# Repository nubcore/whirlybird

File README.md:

# whirlybird
Direction Finder, Compass, IMU and Telemetry Transmitter

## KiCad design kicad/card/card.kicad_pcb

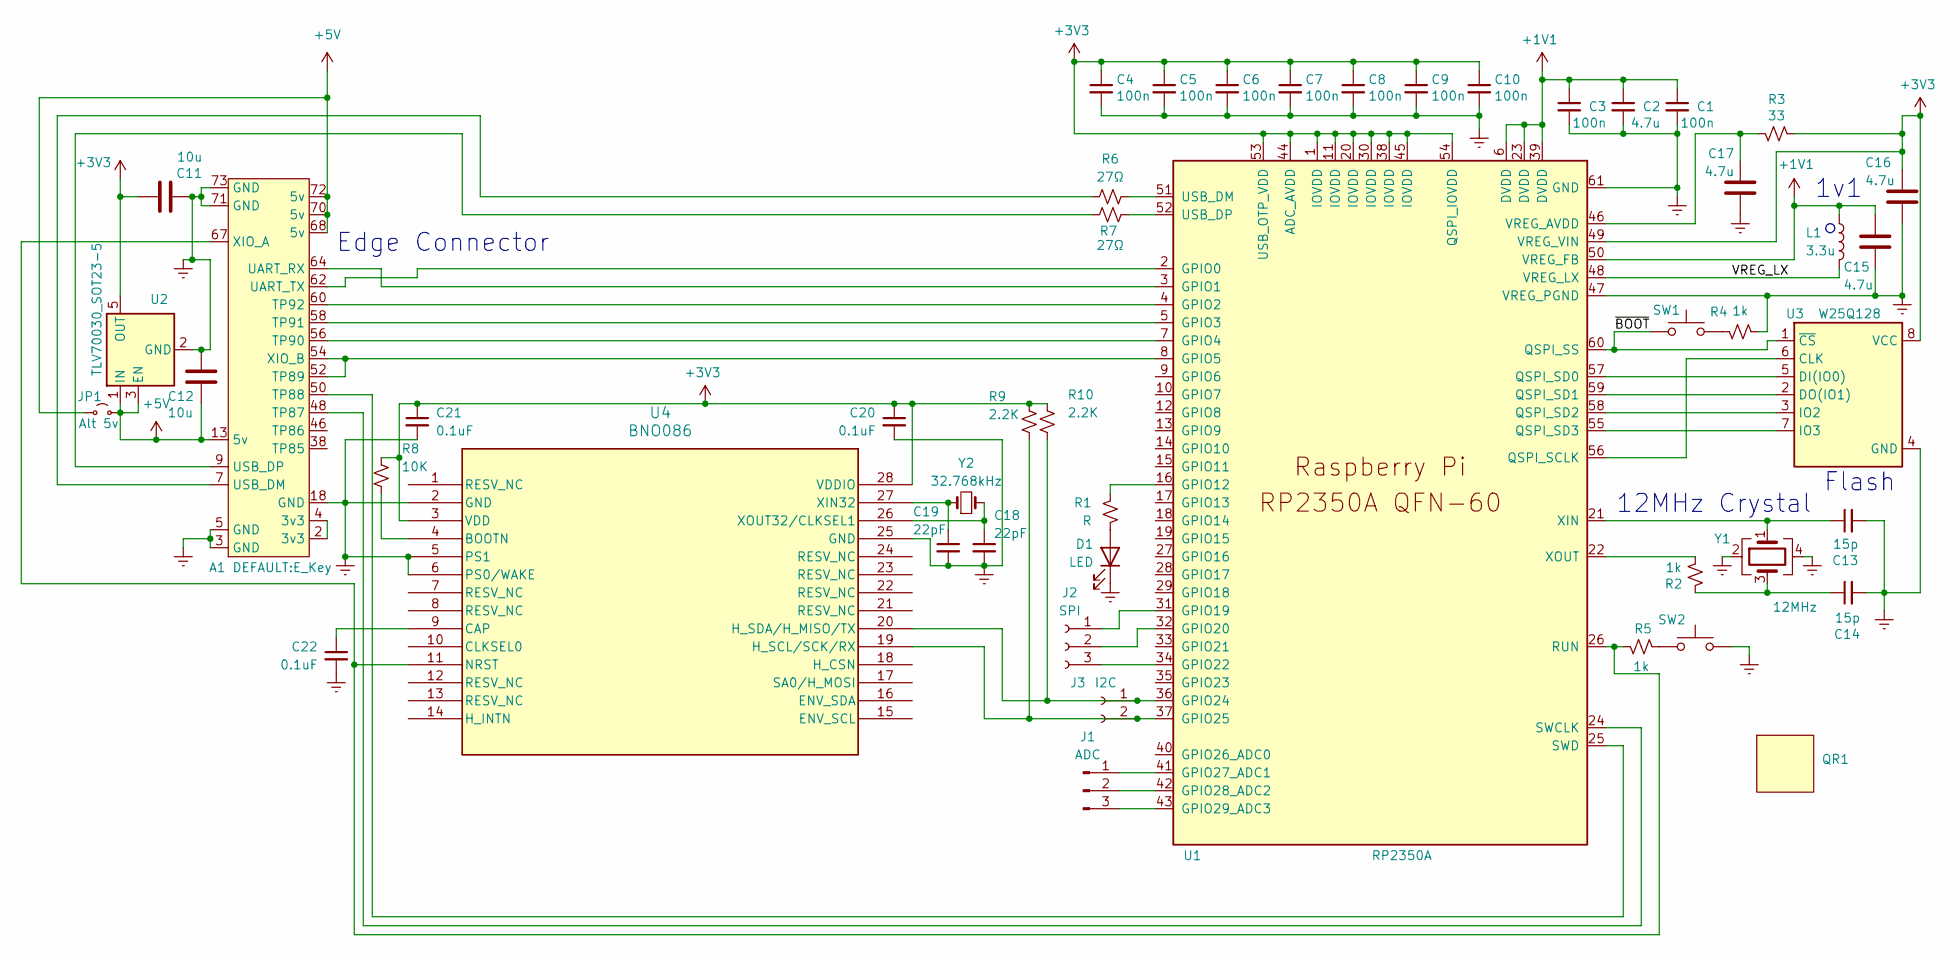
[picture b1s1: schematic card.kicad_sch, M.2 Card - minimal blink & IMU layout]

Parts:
A1: E_Key
C1, C3, C4, C5, C6, C7, C8, C9, C10: 100n; C_0402_1005Metric
C2, C17: 4.7u; C_0402_1005Metric
C11, C12: 10u; C_0805_2012Metric
C13, C14: 15p; C_0402_1005Metric
C15, C16: 4.7u; C_0402_1005Metric_small_pads
C18, C19: 22pF; C_0402_1005Metric
C20, C21, C22: 0.1uF; C_0402_1005Metric
D1: LED; LED_0603_1608Metric_Pad1.05x0.95mm_HandSolder
J1: ADC; PinHeader_1x03_P2.00mm_Vertical
J2: SPI; PinHeader_1x03_P2.00mm_Vertical
J3: I2C; PinHeader_1x02_P2.00mm_Vertical
JP1: Alt 5v; SolderJumper-2_P1.3mm_Open_TrianglePad1.0x1.5mm
L1: 3.3u; L_pol_2016
QR1: QR_8x8
R1: R; R_0603_1608Metric_Pad0.98x0.95mm_HandSolder
R2, R4, R5: 1k; R_0402_1005Metric
R3: 33; R_0402_1005Metric
R6, R7: 27Ω; R_0402_1005Metric
R8: 10K; R_0402_1005Metric
R9, R10: 2.2K; R_0402_1005Metric
SW1: USB_BOOT; SW_Push_1P1T_NO_Vertical_Wuerth_434133025816
SW2: RESET; SW_Push_1P1T_NO_Vertical_Wuerth_434133025816
U1: RP2350A; RP2350-QFN-60-1EP_7x7_P0.4mm_EP3.4x3.4mm_ThermalVias
U2: TLV70030_SOT23-5; SOT-23-5
U3: W25Q128; SOIC-8_5.23x5.23mm_P1.27mm
U4: BNO086; QFN28_BNO086_CEV
Y1: 12MHz; Crystal_SMD_3225-4Pin_3.2x2.5mm
Y2: 32.768kHz; Crystal_SMD_2012-2Pin_2.0x1.2mm

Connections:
+1V1: C1.1, C2.1, C3.1, C15.1, L1.1, U1.6 (DVDD), U1.23 (DVDD), U1.39 (DVDD), U1.50 (VREG_FB)
+3V3: C4.1, C5.1, C6.1, C7.1, C8.1, C9.1, C10.1, C11.1, C16.1, C20.1, C21.1, R3.1, R8.1, R9.1, R10.1, U1.1 (IOVDD), U1.11 (IOVDD), U1.20 (IOVDD), U1.30 (IOVDD), U1.38 (IOVDD), U1.44 (ADC_AVDD), U1.45 (IOVDD), U1.49 (VREG_VIN), U1.53 (USB_OTP_VDD), U1.54 (QSPI_IOVDD), U2.5 (OUT), U3.8 (VCC), U4.3 (VDD), U4.28 (VDDIO); also elsewhere on the board
+5V: A1.13 (5v), A1.68 (5v), A1.70 (5v), A1.72 (5v), C12.2, JP1.1 (A), JP1.2 (B), U2.1 (IN), U2.3 (EN); also elsewhere on the board
/VREG_LX: L1.2, U1.48 (VREG_LX)
/~BOOT: SW1.2, U1.60 (QSPI_SS), U3.1 (~CS)
GND: A1.3 (GND), A1.5 (GND), A1.18 (GND), A1.71 (GND), A1.73 (GND), C1.2, C2.2, C3.2, C4.2, C5.2, C6.2, C7.2, C8.2, C9.2, C10.2, C11.2, C12.1, C13.2, C14.2, C15.2, C16.2, C17.2, C18.2, C19.2, C20.2, C21.2, C22.2, D1.1 (K), R4.2, SW2.1, U1.47 (VREG_PGND), U1.61 (GND), U2.2 (GND), U3.4 (GND), U4.2 (GND), U4.5 (PS1), U4.6 (PS0/WAKE), U4.25 (GND), Y1.2, Y1.4; also elsewhere on the board
unnamed: A1.2 (3v3), A1.4 (3v3)
unnamed: A1.48 (TP87), U1.24 (SWCLK)
unnamed: A1.50 (TP88), U1.25 (SWD)
unnamed: A1.52 (TP89), A1.54 (XIO_B), U1.8 (GPIO5)
unnamed: A1.56 (TP90), U1.7 (GPIO4)
unnamed: A1.58 (TP91), U1.5 (GPIO3)
unnamed: A1.60 (TP92), U1.4 (GPIO2)
unnamed: A1.64 (UART_RX), U1.3 (GPIO1)
unnamed: A1.62 (UART_TX), U1.2 (GPIO0)
unnamed: A1.7 (USB_DM), R6.1
unnamed: A1.9 (USB_DP), R7.1
unnamed: A1.67 (XIO_A), R5.1, U1.26 (RUN), U4.11 (NRST)
unnamed: C14.1, R2.1, Y1.3
unnamed: D1.2 (A), R1.2
unnamed 20: J1.1, U1.41 (GPIO27_ADC1); also elsewhere on the board
unnamed 21: J1.2, U1.42 (GPIO28_ADC2); also elsewhere on the board
unnamed 22: J1.3, U1.43 (GPIO29_ADC3); also elsewhere on the board
unnamed 23: J2.1, U1.31 (GPIO19); also elsewhere on the board
unnamed 24: J2.2, U1.32 (GPIO20); also elsewhere on the board
unnamed 25: J2.3, U1.34 (GPIO22); also elsewhere on the board
unnamed 26: J3.1, R10.2, U1.36 (GPIO24), U4.20 (H_SDA/H_MISO/TX); also elsewhere on the board
unnamed 27: J3.2, R9.2, U1.37 (GPIO25), U4.19 (H_SCL/SCK/RX); also elsewhere on the board
unnamed: R4.1, SW1.1
unnamed: R5.2, SW2.2
unnamed: R1.1, U1.16 (GPIO12)
unnamed: U1.56 (QSPI_SCLK), U3.6 (CLK)
unnamed: U1.57 (QSPI_SD0), U3.5 (DI(IO0))
unnamed: U1.59 (QSPI_SD1), U3.2 (DO(IO1))
unnamed: U1.58 (QSPI_SD2), U3.3 (IO2)
unnamed: U1.55 (QSPI_SD3), U3.7 (IO3)
unnamed: R6.2, U1.51 (USB_DM)
unnamed: R7.2, U1.52 (USB_DP)
unnamed: C17.1, R3.2, U1.46 (VREG_AVDD)
unnamed: C13.1, U1.21 (XIN), Y1.1
unnamed: R2.2, U1.22 (XOUT)
unnamed: R8.2, U4.4 (BOOTN)
unnamed: C22.1, U4.9 (CAP)
unnamed: C19.1, U4.27 (XIN32), Y2.1
unnamed: C18.1, U4.26 (XOUT32/CLKSEL1), Y2.2

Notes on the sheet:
Edge Connector
1v1
Flash
12MHz Crystal

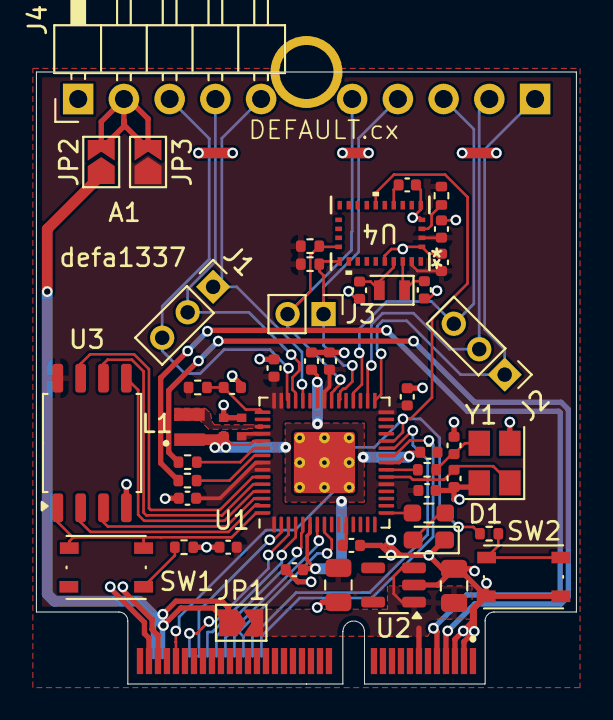
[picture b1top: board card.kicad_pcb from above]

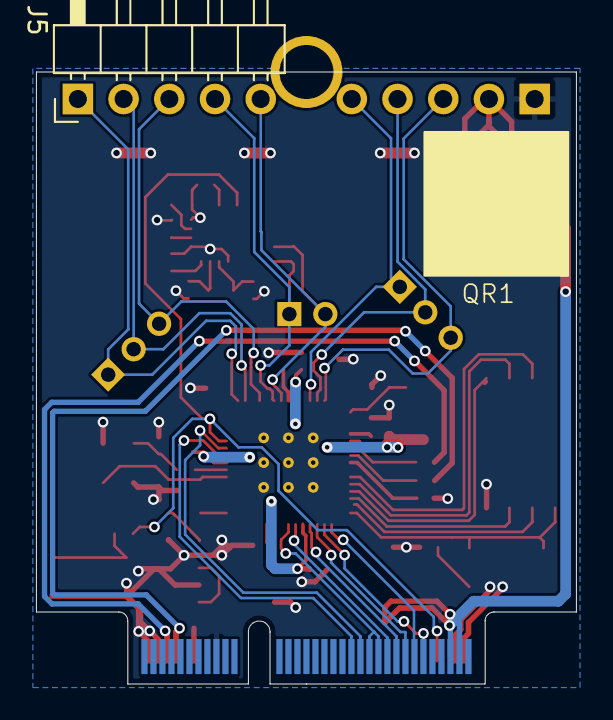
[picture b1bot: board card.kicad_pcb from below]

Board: 2 copper layers, 30.0 x 34.0 mm, 52 parts (2 on the bottom side), 46 nets.

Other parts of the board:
J4, J5: Conn_01x05_Pin; PinHeader_1x05_P2.54mm_Horizontal
JP2: Alt 5V; SolderJumper-2_P1.3mm_Open_TrianglePad1.0x1.5mm
JP3: Alt 3V3; SolderJumper-2_P1.3mm_Open_TrianglePad1.0x1.5mm

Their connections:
+3V3: JP3.1 (A); also elsewhere on the board
+5V: JP2.1 (A); also elsewhere on the board
GND: J4.1; also elsewhere on the board
unnamed 20: J4.5; also elsewhere on the board
unnamed 21: J4.4; also elsewhere on the board
unnamed 22: J4.3; also elsewhere on the board
unnamed 23: J5.1; also elsewhere on the board
unnamed 24: J5.2; also elsewhere on the board
unnamed 25: J5.3; also elsewhere on the board
unnamed 26: J5.4; also elsewhere on the board
unnamed 27: J5.5; also elsewhere on the board
unnamed: J4.2, JP2.2 (B), JP3.2 (B)

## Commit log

2024-10-25 KiCAD Card Project files early test of layout for E Key M.2 IMU board with RP2350A
2024-10-26 getting started images
2024-10-26 minimal "blink" bring up revised schematic and starting with new components to place
2024-10-26 compentents positioned in lower half of PCB
2024-10-27 mostly routed, USB & +5V alt?
2024-10-27 routed, 5V alt and IMU stub
2024-10-28 added 2mm headers and fabrication files
2024-10-29 puck'ish case design
2024-10-29 RS41 Radiosonde MicroPython
2024-10-29 Compass test
2024-10-29 toaster VVV code demo
2024-10-30 BNO08x IMU
2024-10-31 0.1" Breadboard header
2024-10-31 base PCB RGBW layout
2024-10-31 3D model for 5050 LEDs
2024-11-09 5000mAh battery extension
2024-11-09 extruded printable case
2024-11-09 USB port adjust and standoff brace
2024-11-10 laser & 2XL batteries w/blink
2024-11-12 Battey ADC & Buttons
